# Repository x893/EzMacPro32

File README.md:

EzMacPro
========

Port EzMacPro to STM32
Now only Star network tested

Keil project file
application\star_demo\MDK-ARM\star_demo.uvproj

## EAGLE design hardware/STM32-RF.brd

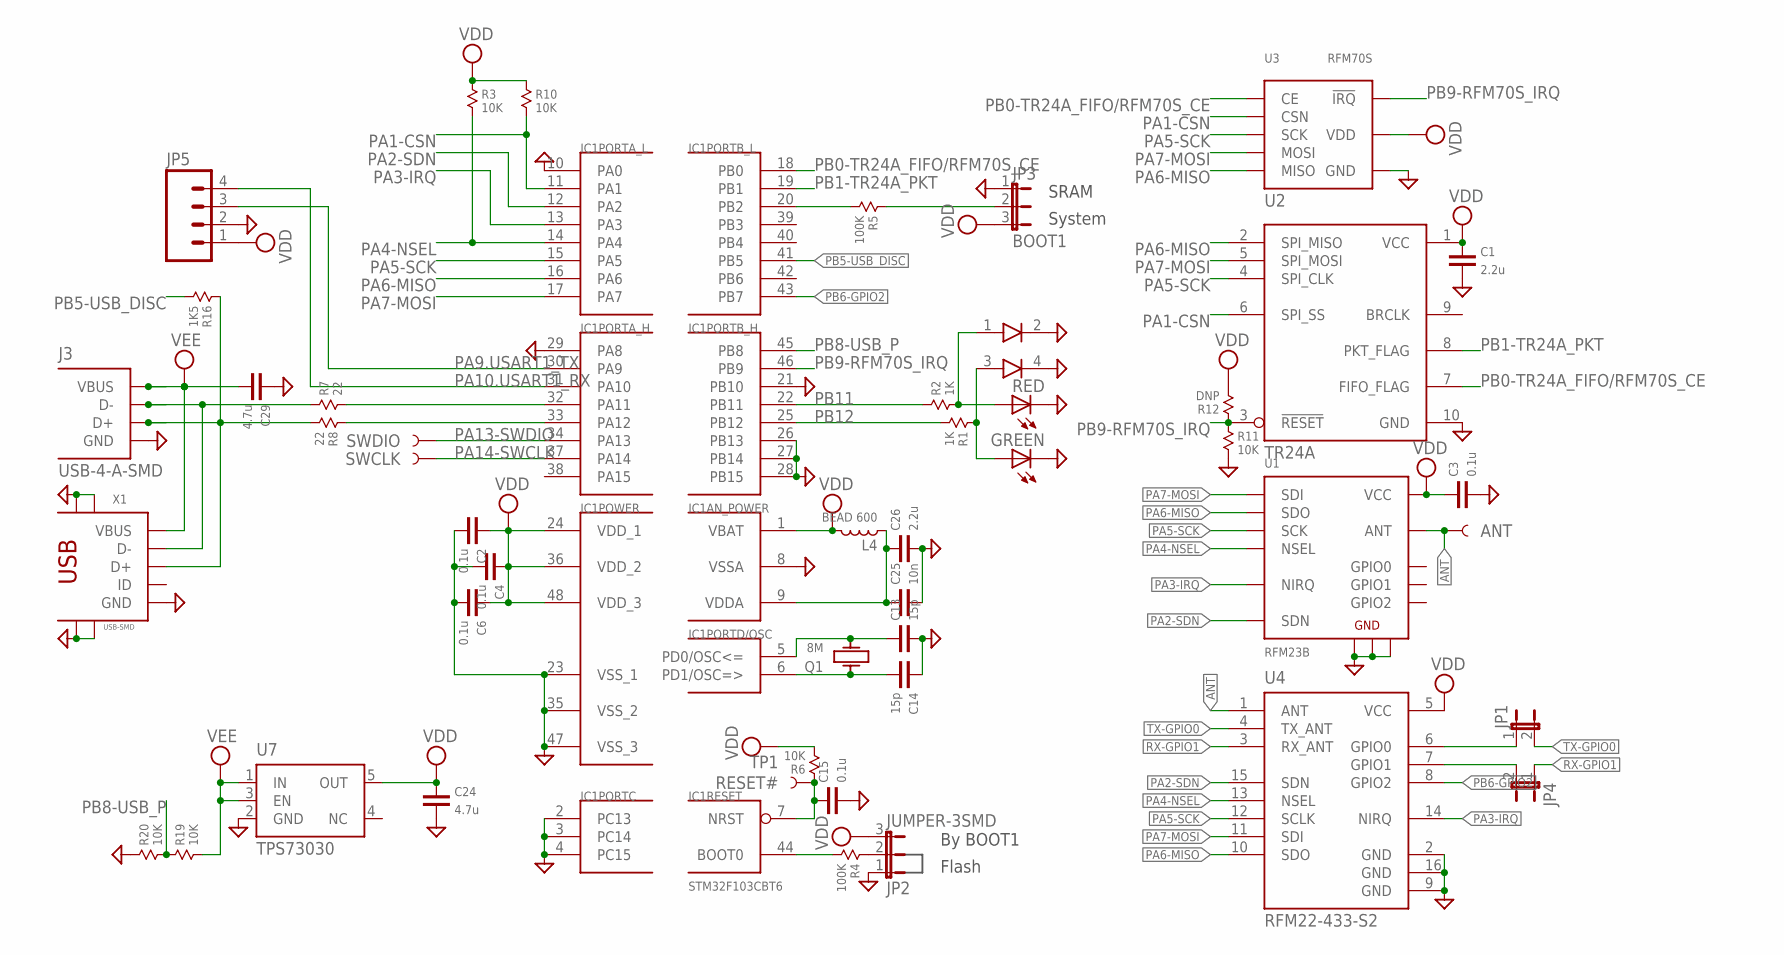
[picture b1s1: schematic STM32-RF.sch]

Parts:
ANT: TEST-POINT1; PAD.1X1
C1, C26: 2.2u; 0603
C2, C3, C4, C6, C15: 0.1u; 0603
C13, C14: 15p; 0603
C24, C29: 4.7u; 0603
C25: 10n; 0603
GREEN: LEDCHIPLED_0603; CHIPLED_0603
IC1: STM32F103CBT6; TQFP48
J3: USB-4-A-SMD; USB-A-SMD
JP1, JP4: JUMPER-2SMD-NO; SJ_2S-NO
JP2: JUMPER-3SMD; SJ_3
JP3: BOOT1; SJ_3
JP5: M04PTH; 1X04
L4: BEAD 600; 0603
Q1: 8M; KX-9A
R1, R2: 1K; 0603
R3, R6, R10, R11, R19, R20: 10K; 0603
R4, R5: 100K; 0603
R7, R8: 22; 0603
R12: DNP; 0603
R16: 1K5; 0603
RED: LEDCHIPLED_0603; CHIPLED_0603
RESET#: TP1; PAD.1X1
SWCLK: TEST-POINT1; PAD.1X1
SWDIO: TEST-POINT1; PAD.1X1
U1: RFM23B; RFM2X
U2: TR24A
U3: RFM70S
U4: RFM22-433-S2; RFM2X
U7: TPS73030; SOT23-5
U$1: LED-DUAL-0605
X1: USB-SMD; USB-MINIB

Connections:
ANT: ANT.P$1, U1.1 (ANT), U4.1 (ANT)
BOOT0: IC1.44 (BOOT0), R4.2
GND: C1.1, C2.1, C3.1, C4.1, C6.1, C13.1, C14.2, C15.1, C24.1, C25.1, C26.1, C29.2, GREEN.C, IC1.2 (PC13), IC1.3 (PC14), IC1.4 (PC15), IC1.8 (VSSA), IC1.10 (PA0), IC1.21 (PB10), IC1.23 (VSS_1), IC1.26 (PB13), IC1.27 (PB14), IC1.28 (PB15), IC1.29 (PA8), IC1.35 (VSS_2), IC1.47 (VSS_3), J3.GND, JP2.1, JP3.1, JP5.2, R11.2, R20.1, RED.C, U1.2 (GND), U1.9 (GND), U1.16 (GND), U2.10 (GND), U3.GND, U4.2 (GND), U4.9 (GND), U4.16 (GND), U7.2 (GND), U$1.2, U$1.4, X1.GND, X1.GND@1 (GND), X1.GND@2 (GND), X1.GND@3 (GND), X1.GND@4 (GND)
LED-RED: R2.2, RED.A, U$1.1
unnamed: C25.2, C26.2, IC1.9 (VDDA), L4.1
unnamed: JP1.1, U4.6 (GPIO0)
unnamed: GREEN.A, R1.1, U$1.3
unnamed: JP4.2, U4.7 (GPIO1)
unnamed: JP2.2, R4.1
unnamed: JP3.2, R5.1
unnamed: J3.D-, R7.1, X1.D-
unnamed: J3.D+, R8.2, R16.1, X1.D+
OSCIN: C14.1, IC1.6 (PD1/OSC=>), Q1.1
OSCOUT: C13.2, IC1.5 (PD0/OSC<=), Q1.3 (2)
PA1-CSN: IC1.11 (PA1), R10.2, U2.6 (SPI_SS), U3.CSN
PA2-SDN: IC1.12 (PA2), U1.15 (SDN), U4.15 (SDN)
PA3-IRQ: IC1.13 (PA3), U1.14 (NIRQ), U4.14 (NIRQ)
PA4-NSEL: IC1.14 (PA4), R3.2, U1.13 (NSEL), U4.13 (NSEL)
PA5-SCK: IC1.15 (PA5), U1.12 (SCK), U2.4 (SPI_CLK), U3.SCK, U4.12 (SCLK)
PA6-MISO: IC1.16 (PA6), U1.10 (SDO), U2.2 (SPI_MISO), U3.MISO, U4.10 (SDO)
PA7-MOSI: IC1.17 (PA7), U1.11 (SDI), U2.5 (SPI_MOSI), U3.MOSI, U4.11 (SDI)
PA9.USART1_TX: IC1.30 (PA9), JP5.3
PA10.USART1_RX: IC1.31 (PA10), JP5.4
PA11: IC1.32 (PA11), R7.2
PA12: IC1.33 (PA12), R8.1
PA13-SWDIO: IC1.34 (PA13), SWDIO.P$1
PA14-SWCLK: IC1.37 (PA14), SWCLK.P$1
PB0-TR24A_FIFO/RFM70S_CE: IC1.18 (PB0), U2.7 (FIFO_FLAG), U3.CE
PB1-TR24A_PKT: IC1.19 (PB1), U2.8 (PKT_FLAG)
PB2/BOOT1: IC1.20 (PB2), R5.2
PB5-USB_DISC: IC1.41 (PB5), R16.2
PB6-GPIO2: IC1.43 (PB7), U4.8 (GPIO2)
PB8-USB_P: IC1.45 (PB8), R19.1, R20.2
PB9-RFM70S_IRQ: IC1.46 (PB9), R11.1, R12.1, U2.3 (!RESET), U3.IRQ (!IRQ)
PB11: IC1.22 (PB11), R2.1
PB12: IC1.25 (PB12), R1.2
RESET#: C15.2, IC1.7 (NRST), R6.1, RESET#.P$1
RX-GPIO1: JP4.1, U4.3 (RX_ANT)
TX-GPIO0: JP1.2, U4.4 (TX_ANT)
VDD: C1.2, C2.2, C3.2, C4.2, C6.2, C24.2, IC1.1 (VBAT), IC1.24 (VDD_1), IC1.36 (VDD_2), IC1.48 (VDD_3), JP2.3, JP3.3, JP5.1, L4.2, R3.1, R6.2, R10.1, R12.2, U1.5 (VCC), U2.1 (VCC), U3.VDD, U4.5 (VCC), U7.5 (OUT)
VEE: C29.1, J3.VUSB (VBUS), R19.2, U7.1 (IN), U7.3 (EN), X1.VBUS

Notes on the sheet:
Flash
By BOOT1
System
SRAM

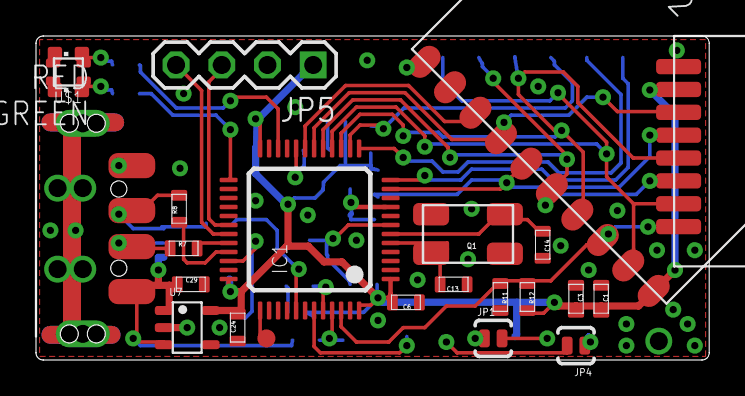
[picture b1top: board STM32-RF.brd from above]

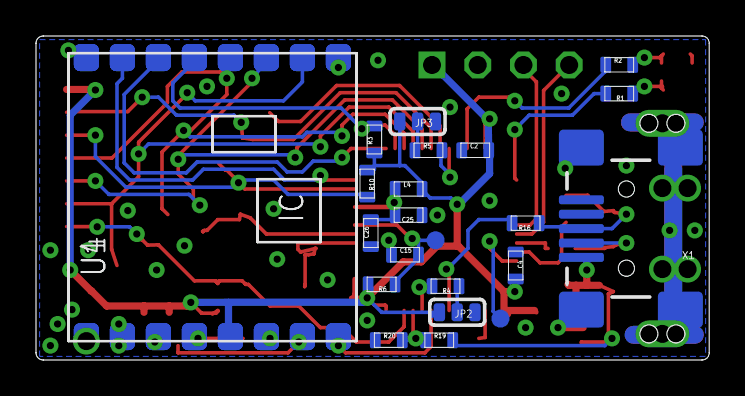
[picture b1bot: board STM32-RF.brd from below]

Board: 2 copper layers, 37.4 x 18.0 mm, 48 parts (23 on the bottom side), 41 nets.

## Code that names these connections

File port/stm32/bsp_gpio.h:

#ifndef __GPIO_H__
#define __GPIO_H__

#include <stdint.h>

#define PIN_NUMBER(p)		((uint8_t)(p & 0x0F))
#define PIN_MASK(p)			((uint16_t)1 << (p & 0x0F))
#define PIN_PORT(p) 		((GPIO_TypeDef *)(((uint32_t)(p & 0xF0) << 6) + GPIOA_BASE))
#define PIN_MASK_MODE(m, p)	((uint32_t)(m & 0x0F) << ((p & 0x07) << 2))

#ifdef STM32F10X_MD
	#define MODE_Analog				(GPIO_Mode_AIN)
	#define MODE_Input				(GPIO_Mode_IN_FLOATING)
	#define MODE_Input_PD			(GPIO_Mode_IPD)
	#define MODE_Input_PU			(GPIO_Mode_IPU)

	#define MODE_PushPull_2M		(GPIO_Mode_Out_PP | GPIO_Speed_2MHz)
	#define MODE_PushPull_10M		(GPIO_Mode_Out_PP | GPIO_Speed_10MHz)
	#define MODE_PushPull_50M		(GPIO_Mode_Out_PP | GPIO_Speed_50MHz)

	#define MODE_OpenDrain_2M		(GPIO_Mode_Out_OD | GPIO_Speed_2MHz)
	#define MODE_OpenDrain_10M		(GPIO_Mode_Out_OD | GPIO_Speed_10MHz)
	#define MODE_OpenDrain_50M		(GPIO_Mode_Out_OD | GPIO_Speed_50MHz)

	#define MODE_AltPushPull_2M		(GPIO_Mode_AF_PP | GPIO_Speed_2MHz)
	#define MODE_AltPushPull_10M	(GPIO_Mode_AF_PP | GPIO_Speed_10MHz)
	#define MODE_AltPushPull_50M	(GPIO_Mode_AF_PP | GPIO_Speed_50MHz)

	#define MODE_AltOpenDrain_2M	(GPIO_Mode_AF_OD | GPIO_Speed_2MHz)
	#define MODE_AltOpenDrain_10M	(GPIO_Mode_AF_OD | GPIO_Speed_10MHz)
	#define MODE_AltOpenDrain_50M	(GPIO_Mode_AF_OD | GPIO_Speed_50MHz)

	#define pinLow(pin)		PIN_PORT(pin)->BRR  = PIN_MASK(pin)
	#define pinHigh(pin)	PIN_PORT(pin)->BSRR = PIN_MASK(pin)

#else
#ifdef STM32L1XX_MD

	#define MODE_Analog				(GPIO_Mode_AN)
	#define MODE_Input				(GPIO_Mode_IN | (GPIO_PuPd_NOPULL << 6))
	#define MODE_Input_PD			(GPIO_Mode_IN | (GPIO_PuPd_UP << 6))
	#define MODE_Input_PU			(GPIO_Mode_IN | (GPIO_PuPd_DOWN << 6))

	#define MODE_PushPull_2M		(GPIO_Mode_OUT | (GPIO_OType_PP << 2) | (GPIO_Speed_2MHz << 4))
	#define MODE_PushPull_10M		(GPIO_Mode_OUT | (GPIO_OType_PP << 2) | (GPIO_Speed_10MHz << 4))
	#define MODE_PushPull_50M		(GPIO_Mode_OUT | (GPIO_OType_PP << 2) | (GPIO_Speed_40MHz << 4))

	#define MODE_OpenDrain_2M		(GPIO_Mode_OUT | (GPIO_OType_OD << 2) | (GPIO_Speed_2MHz << 4))
	#define MODE_OpenDrain_10M		(GPIO_Mode_OUT | (GPIO_OType_OD << 2) | (GPIO_Speed_10MHz << 4))
	#define MODE_OpenDrain_50M		(GPIO_Mode_OUT | (GPIO_OType_OD << 2) | (GPIO_Speed_40MHz << 4))

	#define MODE_AltPushPull_2M		(GPIO_Mode_AF | (GPIO_OType_PP << 2) | (GPIO_Speed_2MHz << 4))
	#define MODE_AltPushPull_10M	(GPIO_Mode_AF | (GPIO_OType_PP << 2) | (GPIO_Speed_10MHz << 4))
	#define MODE_AltPushPull_50M	(GPIO_Mode_AF | (GPIO_OType_PP << 2) | (GPIO_Speed_40MHz << 4))

	#define MODE_AltOpenDrain_2M	(GPIO_Mode_AF | (GPIO_OType_OD << 2) | (GPIO_Speed_2MHz << 4))
	#define MODE_AltOpenDrain_10M	(GPIO_Mode_AF | (GPIO_OType_OD << 2) | (GPIO_Speed_10MHz << 4))
	#define MODE_AltOpenDrain_50M	(GPIO_Mode_AF | (GPIO_OType_OD << 2) | (GPIO_Speed_40MHz << 4))

	#define pinLow(pin)		PIN_PORT(pin)->BSRRH = PIN_MASK(pin)
	#define pinHigh(pin)	PIN_PORT(pin)->BSRRL = PIN_MASK(pin)

#endif
#endif

#define PA0		0x00
#define PA1		0x01
#define PA2		0x02
#define PA3		0x03
#define PA4		0x04
#define PA5		0x05
#define PA6		0x06
#define PA7		0x07
#define PA8		0x08
#define PA9		0x09
#define PA10	0x0A
#define PA11	0x0B
#define PA12	0x0C
#define PA13	0x0D
#define PA14	0x0E
#define PA15	0x0F

#define PB0		0x10
#define PB1		0x11
#define PB2		0x12
#define PB3		0x13
#define PB4		0x14
#define PB5		0x15
#define PB6		0x16
#define PB7		0x17
#define PB8		0x18
#define PB9		0x19
#define PB10	0x1A
#define PB11	0x1B
#define PB12	0x1C
#define PB13	0x1D
#define PB14	0x1E
#define PB15	0x1F

#define PC0		0x20
#define PC1		0x21
#define PC2		0x22
#define PC3		0x23
#define PC4		0x24
#define PC5		0x25
#define PC6		0x26
#define PC7		0x27
#define PC8		0x28
#define PC9		0x29
#define PC10	0x2A
#define PC11	0x2B
#define PC12	0x2C
#define PC13	0x2D
#define PC14	0x2E
#define PC15	0x2F

void pinMode	( uint8_t pin, uint8_t mode );

#endif

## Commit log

2013-05-12 Fix timimng and add TRACE
2013-05-12 Change Readme
2013-05-12 Fixup files. Add p2p examples
2013-05-12 Add missing file
2013-05-12 Initial commit for STM32L series
